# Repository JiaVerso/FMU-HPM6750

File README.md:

# FMU-HPM6750 — RISC-V Flight Controller (HPM6750IVM2)

A Pixhawk-compatible flight controller built around the **HPMicro HPM6750IVM2**
(dual-core RISC-V, 816 MHz, 289-ball BGA) and running the official PX4 port
`px4_fmu-v6xhpm`.

## Highlights

| Item | Value |
| --- | --- |
| MCU | HPM6750IVM2 — dual RISC-V, 816 MHz, 2 MB SRAM |
| IMU | ICM-42688-P (SPI3) + BMI088 (SPI2, redundant) |
| Baro / Mag | BMP390 / BMM350 (I2C3) |
| Storage | 16 MB QSPI NOR (W25Q128), 32 KB FRAM, 2 × 8 KB EEPROM, microSD |
| Power | 5 V input, LTC4417 ORing, MP2315 buck 3.3 V/3 A, LP5907 sensor LDO |
| IO | 8 × PWM, 5 × UART, 3 × I2C, 3 × SPI, 2 × CAN, USB-C (16P) |
| PCB | 8 layers, 1.6 mm, ENIG, impedance-controlled |

## Repository layout

```
FMU-HPM6750/
├─ FMU-H6750.kicad_pro        # KiCad project
├─ FMU-H6750.kicad_sch        # root sheet (7 sub-sheets)
├─ 02_mcu.kicad_sch           # MCU + clocks + reset/boot + decoupling
├─ 03_power.kicad_sch         # 5V input, ORing, buck, LDO, sensing
├─ 04_storage.kicad_sch       # QSPI flash, microSD, FRAM, EEPROM
├─ 05_sensors.kicad_sch       # IMU / baro / mag + heater
├─ 06_comms.kicad_sch         # USB-C 16P, CAN, telemetry, RC
├─ 07_actuator.kicad_sch      # PWM outputs, buzzer, safety switch, LEDs
├─ 08_connectors.kicad_sch    # connector pin-out reference
├─ 02b_decoupling.kicad_sch   # VDD/VSS decoupling (standalone)
├─ 02c_power_unit.kicad_sch   # power unit + decoupling (standalone)
├─ FMU-H6750.kicad_pcb        # PCB layout (BGA-289 placed, unrouted)
├─ FMU_H6750.kicad_sym        # project symbol library
└─ sym-lib-table              # library table
```

## Pin assignment

The MCU symbol uses **HPM pad names** as pin numbers (e.g. `PZ01`, `PE27`) so they
map 1:1 onto the PX4 `GPIO_PORTx|GPIO_PINn` macros. 289 balls are all present in
the schematic; the 113 pins used by the firmware carry global labels, the
remaining ones are marked no-connect.

## Getting started

```bash
git clone https://github.com/JiaVerso/FMU-HPM6750.git
cd FMU-HPM6750
# open FMU-H6750.kicad_pro with KiCad 8.0 or newer
```

Firmware (PX4):

```bash
git clone https://github.com/hpmicro/PX4-Autopilot -b feature/px4_v1.16.0_hpm_fmuv6x
cd PX4-Autopilot
make px4_fmu-v6xhpm_default
```

## Status

- [x] Schematic complete, ERC-style self check passed (0 errors, 0 floating pins)
- [x] All 289 BGA balls accounted for
- [ ] PCB routing (BGA fan-out in progress)
- [ ] Hardware bring-up

## License

Hardware design files released under **CERN-OHL-S-1.2**.
PX4 firmware components remain under their original licenses.

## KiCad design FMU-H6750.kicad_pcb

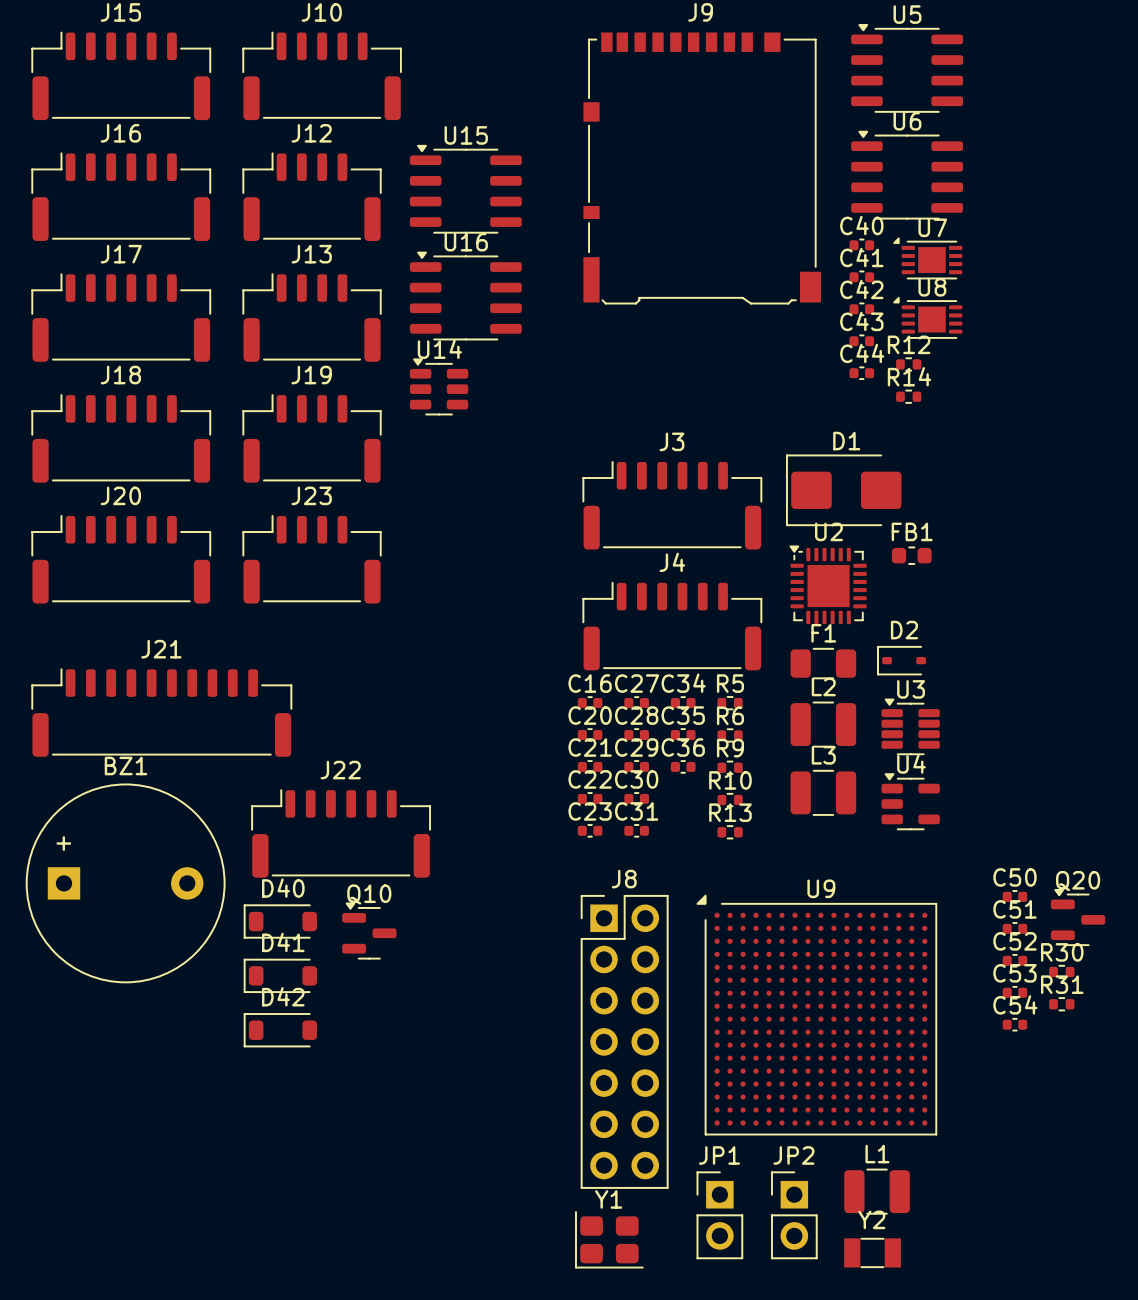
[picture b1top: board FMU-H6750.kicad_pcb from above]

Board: 2 copper layers, 76 parts (0 on the bottom side), 29 nets, no tracks yet.

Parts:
BZ1: 5V buzzer; Buzzer_12x9.5RM7.6
C16, C22, C27, C28, C29, C30, C31, C35, C40, C42, C43, C44, C50, C52, C53, C54: 100nF; C_0402_1005Metric
C20, C21: 22uF; C_0402_1005Metric
C23: 1uF; C_0402_1005Metric
C34: 10uF; C_0402_1005Metric
C36: 10nF; C_0402_1005Metric
C41: 4.7uF; C_0402_1005Metric
C51: 2.2uF; C_0402_1005Metric
D1: SMBJ5.0A; D_SMB
D2: BAT54; D_SOD-323
D40: LED LED_RED; D_SOD-123
D41: LED LED_GREEN; D_SOD-123
D42: LED LED_BLUE; D_SOD-123
F1: 3A fuse; Fuse_1206_3216Metric
FB1: 600R; L_0603_1608Metric
J3: POWER1; JST_GH_SM06B-GHS-TB_1x06-1MP_P1.25mm_Horizontal
J4: POWER2; JST_GH_SM06B-GHS-TB_1x06-1MP_P1.25mm_Horizontal
J8: cJTAG 14P; PinHeader_2x07_P2.54mm_Vertical
J9: TF-01A; microSD_HC_Hirose_DM3AT-SF-PEJM5
J10: USB-C; JST_GH_SM05B-GHS-TB_1x05-1MP_P1.25mm_Horizontal
J12: CAN1; JST_GH_SM04B-GHS-TB_1x04-1MP_P1.25mm_Horizontal
J13: CAN2; JST_GH_SM04B-GHS-TB_1x04-1MP_P1.25mm_Horizontal
J15: TELEM1; JST_GH_SM06B-GHS-TB_1x06-1MP_P1.25mm_Horizontal
J16: TELEM2; JST_GH_SM06B-GHS-TB_1x06-1MP_P1.25mm_Horizontal
J17: TELEM3; JST_GH_SM06B-GHS-TB_1x06-1MP_P1.25mm_Horizontal
J18: GPS; JST_GH_SM06B-GHS-TB_1x06-1MP_P1.25mm_Horizontal
J19: I2C4; JST_GH_SM04B-GHS-TB_1x04-1MP_P1.25mm_Horizontal
J20: SPI EXT; JST_GH_SM06B-GHS-TB_1x06-1MP_P1.25mm_Horizontal
J21: FMU PWM OUT; JST_GH_SM10B-GHS-TB_1x10-1MP_P1.25mm_Horizontal
J22: SAFETY; JST_GH_SM06B-GHS-TB_1x06-1MP_P1.25mm_Horizontal
J23: RC IN/OUT; JST_GH_SM04B-GHS-TB_1x04-1MP_P1.25mm_Horizontal
JP1: BOOT0=1; PinHeader_1x02_P2.54mm_Vertical
JP2: BOOT1=1; PinHeader_1x02_P2.54mm_Vertical
L1, L2: 4.7uH; L_1210_3225Metric
L3: 10uH CMC; L_1210_3225Metric
Q10, Q20: AO3400; SOT-23
R5, R6: 1k; R_0402_1005Metric
R9: 33k; R_0402_1005Metric
R10: 22k; R_0402_1005Metric
R12, R14, R31: 10k; R_0402_1005Metric
R13: 0R; R_0402_1005Metric
R30: 10R 1W; R_0402_1005Metric
U2: LTC4417; QFN-24-1EP_4x4mm_P0.5mm_EP2.6x2.6mm
U3: MP2315 3A; TSOT-23-8
U4: LP5907-3.3; SOT-23-5
U5: W25Q128JVSIQ; SOIC-8_3.9x4.9mm_P1.27mm
U6: FM25V02A; SOIC-8_3.9x4.9mm_P1.27mm
U7, U8: 24LC64; DFN-8-1EP_3x2mm_P0.5mm_EP1.7x1.6mm
U9: HPM6750IVM2; LFBGA-289_14x14mm_Layout17x17_P0.8mm
U14: USBLC6-2SC6; SOT-23-6
U15, U16: TJA1051T/3; SOIC-8_3.9x4.9mm_P1.27mm
Y1: 24MHz; Crystal_SMD_3225-4Pin_3.2x2.5mm
Y2: 32.768kHz; Crystal_SMD_3215-2Pin_3.2x1.5mm

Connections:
ADC_5V: C29.1, R9.2, R10.1
BOOT_CAP: C16.1, U3.6 (BST)
BZ_A: BZ1.2, Q10.3 (D)
CAN0_H: J12.2, U15.7 (CANH)
CAN0_L: J12.3, U15.6 (CANL)
CAN1_H: J13.2, U16.7 (CANH)
CAN1_L: J13.3, U16.6 (CANL)
GND: C20.2, C21.2, C22.2, C23.2, C27.2, C28.2, C29.2, C30.2, C31.2, C34.2, C35.2, C36.2, C40.2, C41.2, C42.2, C43.2, C44.2, C50.2, C51.2, C52.2, C53.2, C54.2, D1.2, J3.3, J3.4, J4.3, J4.4, J8.3, J8.5, J8.9, J8.11, J9.6, J10.5, J12.4, J13.4, J15.6, J16.6, J17.6, J18.6, J19.4, J20.6, J21.9, J22.4, J23.4, Q10.2 (S), Q20.2 (S), R10.2, R31.2, U2.3 (GND), U3.3 (GND), U4.2 (GND), U5.4 (GND), U6.3 (WP#), U6.4 (GND), U7.1 (A0), U7.2 (A1), U7.3 (A2), U7.4 (GND), U7.7 (WP), U8.1 (A0), U8.2 (A1), U8.3 (A2), U8.4 (GND), U8.7 (WP), U14.2 (GND), U15.2 (GND), U16.2 (GND)
HEATER: Q20.1 (G), R31.1
I2C0_SCL: J18.4, U8.6 (SCL)
I2C0_SDA: J18.5, U8.5 (SDA)
unnamed: Q20.3 (D), R30.2
PWR_C_SENSE: C28.1, R6.2
PWR_C_SENSE_J: J3.5, J4.5, R6.1
PWR_V_SENSE: C27.1, R5.2
PWR_V_SENSE_J: J3.6, J4.6, R5.1
SW_NODE: C16.2, L2.1, U3.4 (SW)
USB_DN: J10.2, U14.3 (IO2)
USB_DP: J10.3, U14.1 (IO1)
USB_VBUS: J10.1, U2.2 (VIN2), U14.4 (VBUS)
VBAT_RTC: C31.1, D2.2
VDDA_3V3: C34.1, C35.1, FB1.2, R13.1
VDD_3V3: C20.1, C21.1, C22.1, C40.1, C41.1, C42.1, C43.1, C44.1, D2.1, J8.1, J9.4, J20.1, J22.1, JP1.2, JP2.2, L2.2, R12.1, R14.1, U2.5 (EN), U3.5 (FB), U4.1 (IN), U4.3 (EN), U5.8 (VCC), U6.7 (HOLD#), U6.8 (VDD), U7.8 (VCC), U8.8 (VCC), U15.5 (VIO), U16.5 (VIO)
VDD_3V3_SENS: C23.1, C50.1, C51.1, C52.1, C53.1, C54.1, FB1.1, U4.5 (OUT)
VDD_5V: D1.1, F1.2, L3.1
VDD_5V_CM: L3.2, U2.1 (VIN1)
VDD_5V_IN: F1.1, J3.1, J3.2, J4.1, J4.2
VDD_5V_SYS: BZ1.1, J12.1, J13.1, J15.1, J16.1, J17.1, J18.1, J19.1, J23.1, R9.1, R30.1, U2.4 (VOUT), U3.1 (IN), U3.2 (EN), U15.3 (VCC), U16.3 (VCC)
VREF_3V3: C36.1, R13.2

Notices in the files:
README.md:
License: CERN-OHL-S 1.2
